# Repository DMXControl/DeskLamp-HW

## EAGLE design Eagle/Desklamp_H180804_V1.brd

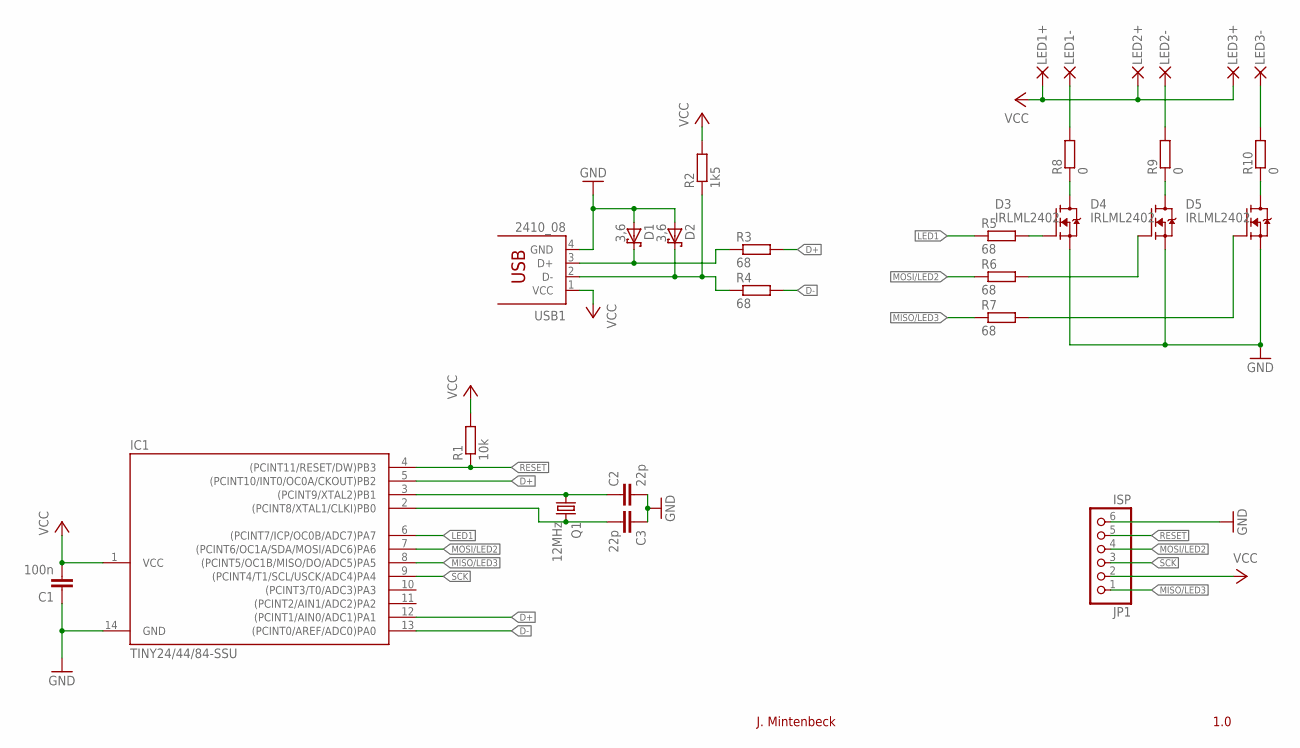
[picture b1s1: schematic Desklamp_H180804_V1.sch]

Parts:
C1: 100n; C0805; PARTNO CC0805KRX7R9BB104
C2, C3: 22p; C0805; PARTNO VVS-SMD COG 50 V 22 PF G0805
D1, D2: 3,6; SOT23; PARTNO BZX84C3V6
D3, D4, D5: IRLML2402; SOT23; PARTNO IRLML2402PBF
IC1: TINY24/44/84-SSU; SOIC14; PARTNO ATTINY44ASSU
JP1: ISP; 1X06M
PAD1: LED1+; SMD1,27-2,54
PAD2: LED1-; SMD1,27-2,54
PAD3: LED2+; SMD1,27-2,54
PAD4: LED2-; SMD1,27-2,54
PAD5: LED3+; SMD1,27-2,54
PAD6: LED3-; SMD1,27-2,54
Q1: 12MHz; HC49UP; PARTNO 12.000MHZ 49USMX/30/50/40/18PF/ATF
R1: 10k; R0805; PARTNO RC0805 FR-07 10 K
R2: 1k5; R0805; PARTNO RC0805 FR-07 1,5 K
R3, R4, R5, R6, R7: 68; R0805; PARTNO RC0805 FR-07 68 R
R8, R9, R10: 0; R0805; PARTNO RC0805 FR-07 0 R
USB1: 2410_08; PARTNO 2410 08

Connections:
D+: IC1.5 ((PCINT10/INT0/OC0A/CKOUT)PB2), IC1.12 ((PCINT1/AIN0/ADC1)PA1), R3.2
D-: IC1.13 ((PCINT0/AREF/ADC0)PA0), R4.2
GND: C1.1, C2.2, C3.1, D1.1 (A), D2.1 (A), D3.2 (S), D4.2 (S), D5.2 (S), IC1.14 (GND), JP1.6, USB1.4 (GND)
LED1: IC1.6 ((PCINT7/ICP/OC0B/ADC7)PA7), R5.1
MISO/LED3: IC1.8 ((PCINT5/OC1B/MISO/DO/ADC5)PA5), JP1.1, R7.1
MOSI/LED2: IC1.7 ((PCINT6/OC1A/SDA/MOSI/ADC6)PA6), JP1.4, R6.1
unnamed: D3.3 (D), R8.1
unnamed: D4.3 (D), R9.1
unnamed: D4.1 (G), R6.2
unnamed: D5.3 (D), R10.1
unnamed: PAD2.1, R8.2
unnamed: D1.3 (C), R3.1, USB1.3 (D+)
unnamed: D2.3 (C), R2.1, R4.1, USB1.2 (D-)
unnamed: C3.2, IC1.2 ((PCINT8/XTAL1/CLKI)PB0), Q1.2
unnamed: C2.1, IC1.3 ((PCINT9/XTAL2)PB1), Q1.1
unnamed: D3.1 (G), R5.2
unnamed: D5.1 (G), R7.2
unnamed: PAD4.1, R9.2
unnamed: PAD6.1, R10.2
RESET: IC1.4 ((PCINT11/RESET/DW)PB3), JP1.5, R1.1
SCK: IC1.9 ((PCINT4/T1/SCL/USCK/ADC4)PA4), JP1.3
VCC: C1.2, IC1.1 (VCC), JP1.2, PAD1.1, PAD3.1, PAD5.1, R1.2, R2.2, USB1.1 (VCC)

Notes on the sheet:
J. Mintenbeck
1.0

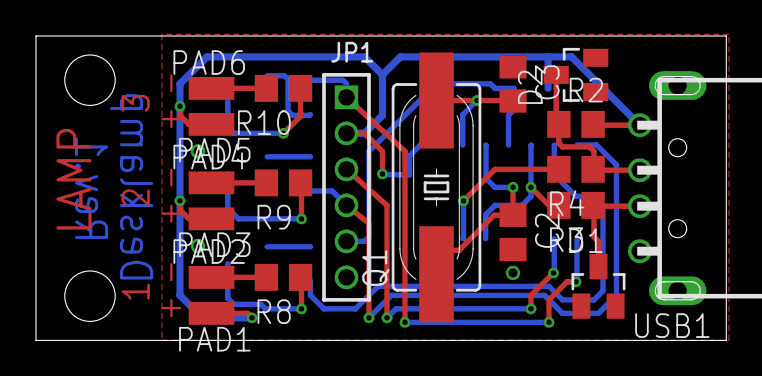
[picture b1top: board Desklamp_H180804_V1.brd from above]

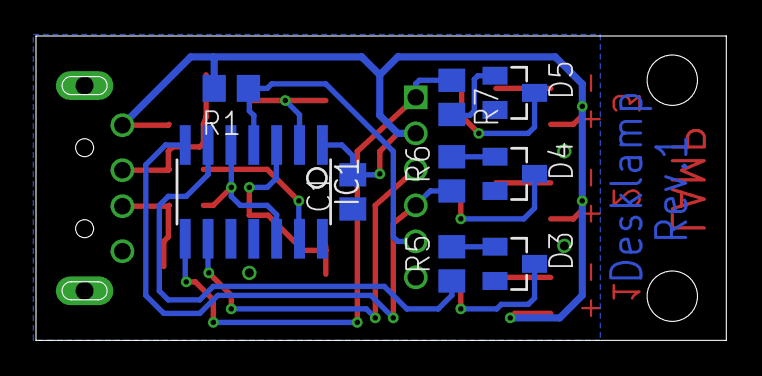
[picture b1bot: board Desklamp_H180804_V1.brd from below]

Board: 2 copper layers, 38.4 x 16.9 mm, 28 parts (9 on the bottom side), 22 nets.

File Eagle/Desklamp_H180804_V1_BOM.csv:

Qty-1,Part References,Value,Package,Mfg Part Num,Mfg Name,VID,Vendor Part Num,Description,Pkg Code,XREF
3,"R8, R9, R10",0,R0805,RC0805 FR-07 0 R,Yageo,RE,SMD-0805 0,00,SMD-Chipwiderstand 0805, 0 Ohm, 1%,0805,REF123
1,"R2",1k5,R0805,RC0805 FR-07 1,5 K,Yageo,RE,SMD-0805 1,50K,SMD-Chipwiderstand 0805, 1,5 K-Ohm, 1%,0805,REF76
2,"D1, D2",3,6,SOT23,BZX84C3V6,Fairchild Semiconductor,RE,SMD ZD 3,6,Chip-Zener-Diode 0,35W 3,6V,SOT23,REF153
1,"R1",10k,R0805,RC0805 FR-07 10 K,Yageo,RE,SMD-0805 10,0K,SMD-Chipwiderstand 0805, 10 K-Ohm, 1%,0805,REF98
1,"Q1",12MHz,HC49UP,12.000MHZ 49USMX/30/50/40/18PF/ATF,Euroquartz,RE,12,0000-HC49-SMD,SMD-Quarz, Grundton, 12,000000 MHz,HC49/US,REF149
2,"C2, C3",22p,C0805,VVS-SMD COG 50 V 22 PF G0805,Yageo,RE,NPO-G0805 22P,SMD-Vielschicht-Keramikkondensator 22P, 5%,0805,REF154
5,"R3, R4, R5, R6, R7",68,R0805,RC0805 FR-07 68 R,Yageo,RE,SMD-0805 68,0,SMD-Chipwiderstand 0805, 68 Ohm, 1%,0805,REF133
1,"C1",100n,C0805,CC0805KRX7R9BB104,Yageo,RE,X7R-G0805 100N,SMD-Vielschicht-Keramikkondensator 100N, 10%,0805,REF150
1,"USB1",2410_08,2410_08,2410 08,Lumberg,RE,LUM 2410-08,USB-Einbaustecker, Typ A, gew., PCB,*,REF151
3,"D3, D4, D5",IRLML2402,SOT23,IRLML2402PBF,International Rectifier,RE,IRLML 2402,SMD-MOSFET, N-LogL, SOT23, 20V, 1.2A,SOT23,REF155
1,"JP1",ISP,1X06M,***PART# '*' NOT FOUND***,*,*,*,*,*,*
1,"PAD1",LED1+,SMD1,27-2,54,***PART# '*' NOT FOUND***,*,*,*,*,*,*
1,"PAD2",LED1-,SMD1,27-2,54,***PART# '*' NOT FOUND***,*,*,*,*,*,*
1,"PAD3",LED2+,SMD1,27-2,54,***PART# '*' NOT FOUND***,*,*,*,*,*,*
1,"PAD4",LED2-,SMD1,27-2,54,***PART# '*' NOT FOUND***,*,*,*,*,*,*
1,"PAD5",LED3+,SMD1,27-2,54,***PART# '*' NOT FOUND***,*,*,*,*,*,*
1,"PAD6",LED3-,SMD1,27-2,54,***PART# '*' NOT FOUND***,*,*,*,*,*,*
1,"IC1",TINY24/44/84-SSU,SOIC14,ATTINY44ASSU,Atmel,RE,ATTINY 44A-SSU,Atmel AVR-RISC-Controller, SOIC-14,SOIC14,REF152

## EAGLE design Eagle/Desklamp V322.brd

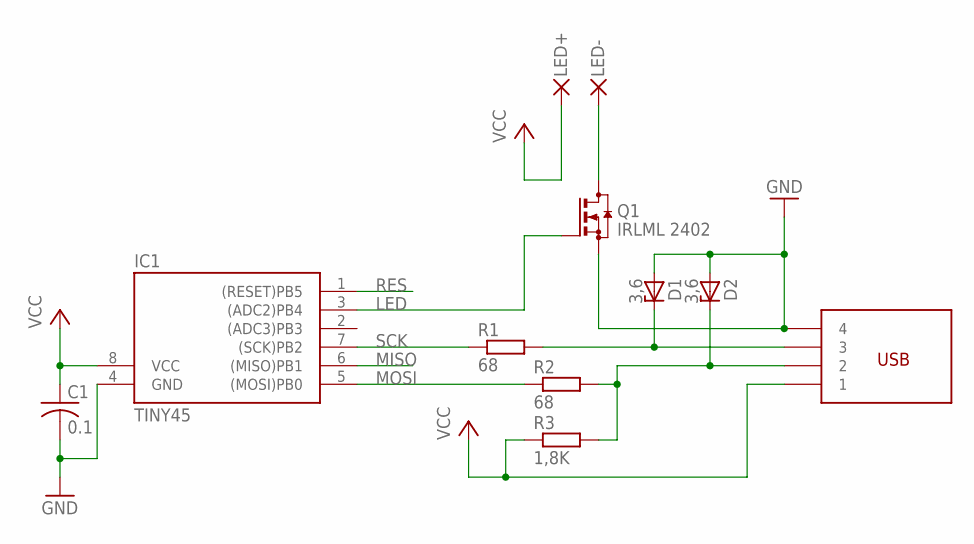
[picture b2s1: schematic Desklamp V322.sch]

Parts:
C1: 0.1; C0805
D1, D2: 3,6; SOT23
IC1: TINY45; SOIC8
PAD7: LED+; SMD1,27-2,54
PAD8: LED-; SMD1,27-2,54
Q1: IRLML 2402; SOT23
R1, R2: 68; R0603
R3: 1,8K; R0603
U$1: USB_A_EDGE

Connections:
GND: C1.2, D1.1 (A), D2.1 (A), IC1.4 (GND), Q1.2 (S), U$1.P$3 (4)
LED: IC1.3 ((ADC2)PB4), Q1.1 (G)
LED-: PAD8.1, Q1.3 (D)
MISO: IC1.6 ((MISO)PB1)
MOSI: IC1.5 ((MOSI)PB0), R2.1
RES: IC1.1 ((RESET)PB5)
SCK: IC1.7 ((SCK)PB2), R1.1
USB2: D2.3 (C), R2.2, R3.2, U$1.P$2 (2)
USB3: D1.3 (C), R1.2, U$1.P$1 (3)
VCC: C1.1, IC1.8 (VCC), PAD7.1, R3.1, U$1.P$4 (1)

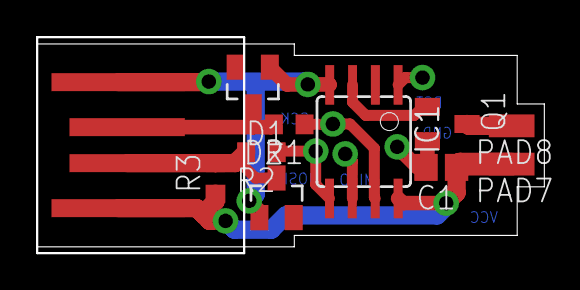
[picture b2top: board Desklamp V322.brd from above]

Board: 2 copper layers, 28.1 x 12.0 mm, 11 parts (0 on the bottom side), 8 nets.

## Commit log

2015-04-18 Warenkorb Mouser hinzugefügt
2015-04-18 modified mouser cart
2016-04-21 - Removed Eagle backup files - Removed old (unproduced) DeskLamp version - Removed Eagle preferences - Removed exported BOM lists (have Mouser carts)
